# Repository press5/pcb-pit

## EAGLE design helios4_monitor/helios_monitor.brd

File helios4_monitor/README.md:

This is a front-panel status LED board for the Helios4.   The connector mounts on the back side of the board to hide the cable.

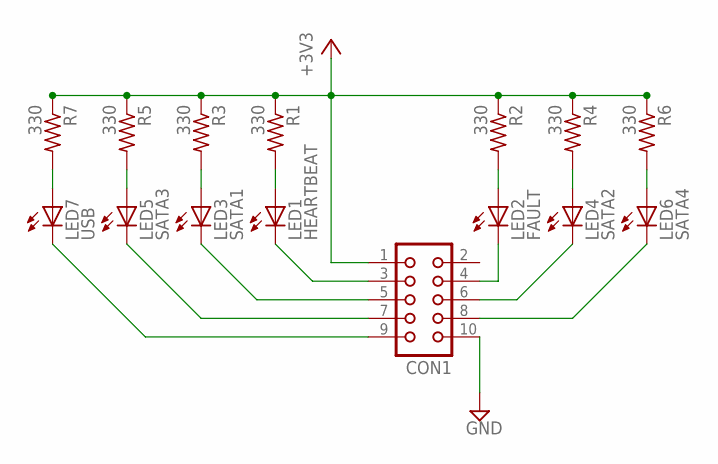
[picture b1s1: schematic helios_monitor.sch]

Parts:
CON1: CON10
LED1: HEARTBEAT; LED5MM
LED2: FAULT; LED5MM
LED3: SATA1; LED5MM
LED4: SATA2; LED5MM
LED5: SATA3; LED5MM
LED6: SATA4; LED5MM
LED7: USB; LED5MM
R1, R2, R3, R4, R5, R6, R7: 330; 0207/10

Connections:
+3V3: CON1.1, R1.1, R2.1, R3.1, R4.1, R5.1, R6.1, R7.1
GND: CON1.10
unnamed: LED1.A, R1.2
unnamed: LED3.A, R3.2
unnamed: LED5.A, R5.2
unnamed: LED7.A, R7.2
unnamed: LED2.A, R2.2
unnamed: LED4.A, R4.2
unnamed: LED6.A, R6.2
unnamed: CON1.3, LED1.K (C)
unnamed: CON1.5, LED3.K (C)
unnamed: CON1.7, LED5.K (C)
unnamed: CON1.9, LED7.K (C)
unnamed: CON1.4, LED2.K (C)
unnamed: CON1.6, LED4.K (C)
unnamed: CON1.8, LED6.K (C)

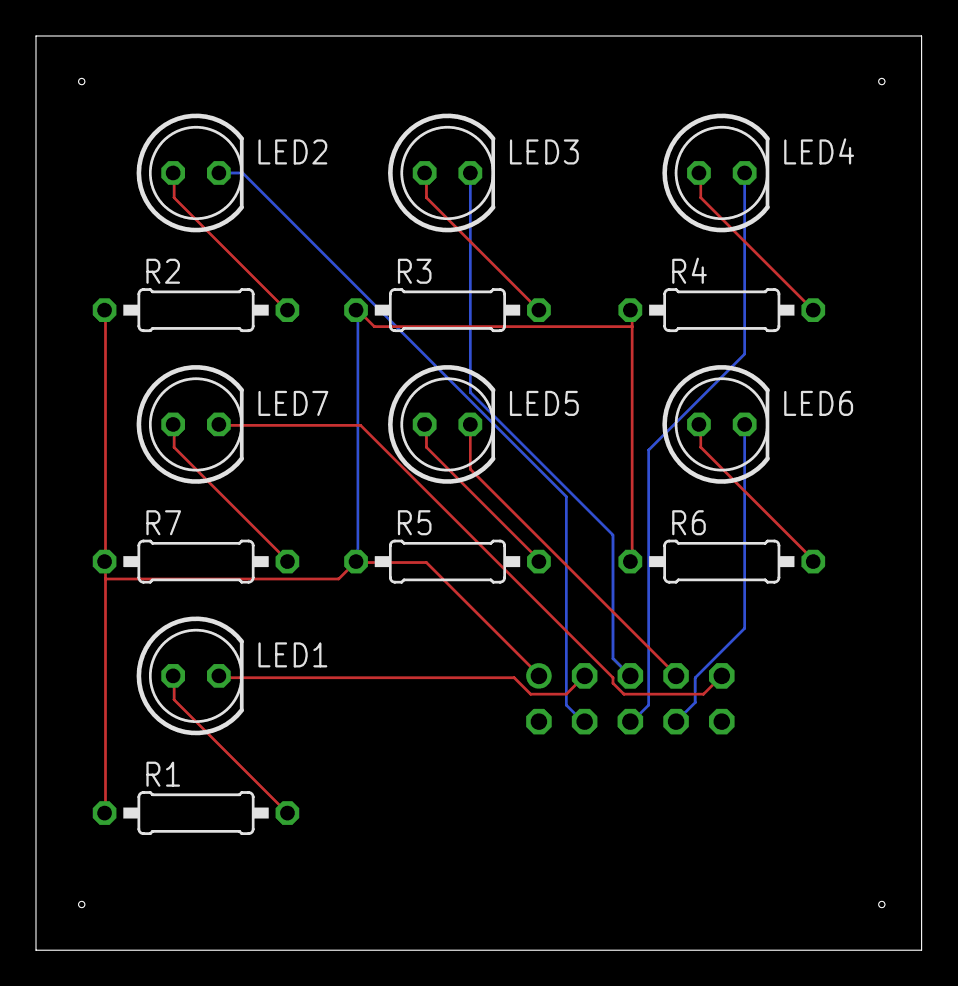
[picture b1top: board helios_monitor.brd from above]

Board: 2 copper layers, 49.2 x 50.8 mm, 15 parts (1 on the bottom side), 15 nets.

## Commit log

2019-01-03 helios4 front panel status led board
